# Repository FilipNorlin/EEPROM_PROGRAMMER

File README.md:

# EEPROM_PROGRAMMER

## Diagram

```mermaid
flowchart TD
    BAT(Battery) --> V_REG(Voltage Regulator)
    V_REG --> Protection(Input Protection)
    USB(USB C) --> Protection
    Protection --> MCU{MCU}
    MCU --> LCD(LCD Display)
    MCU --> Input(Input Controls)
    MCU --> SD(SD Card Reader)
    MCU --> Logic(Logic)
    Logic --> LED(Data LEDs)
    Logic --> EEPROM(EEPROM)

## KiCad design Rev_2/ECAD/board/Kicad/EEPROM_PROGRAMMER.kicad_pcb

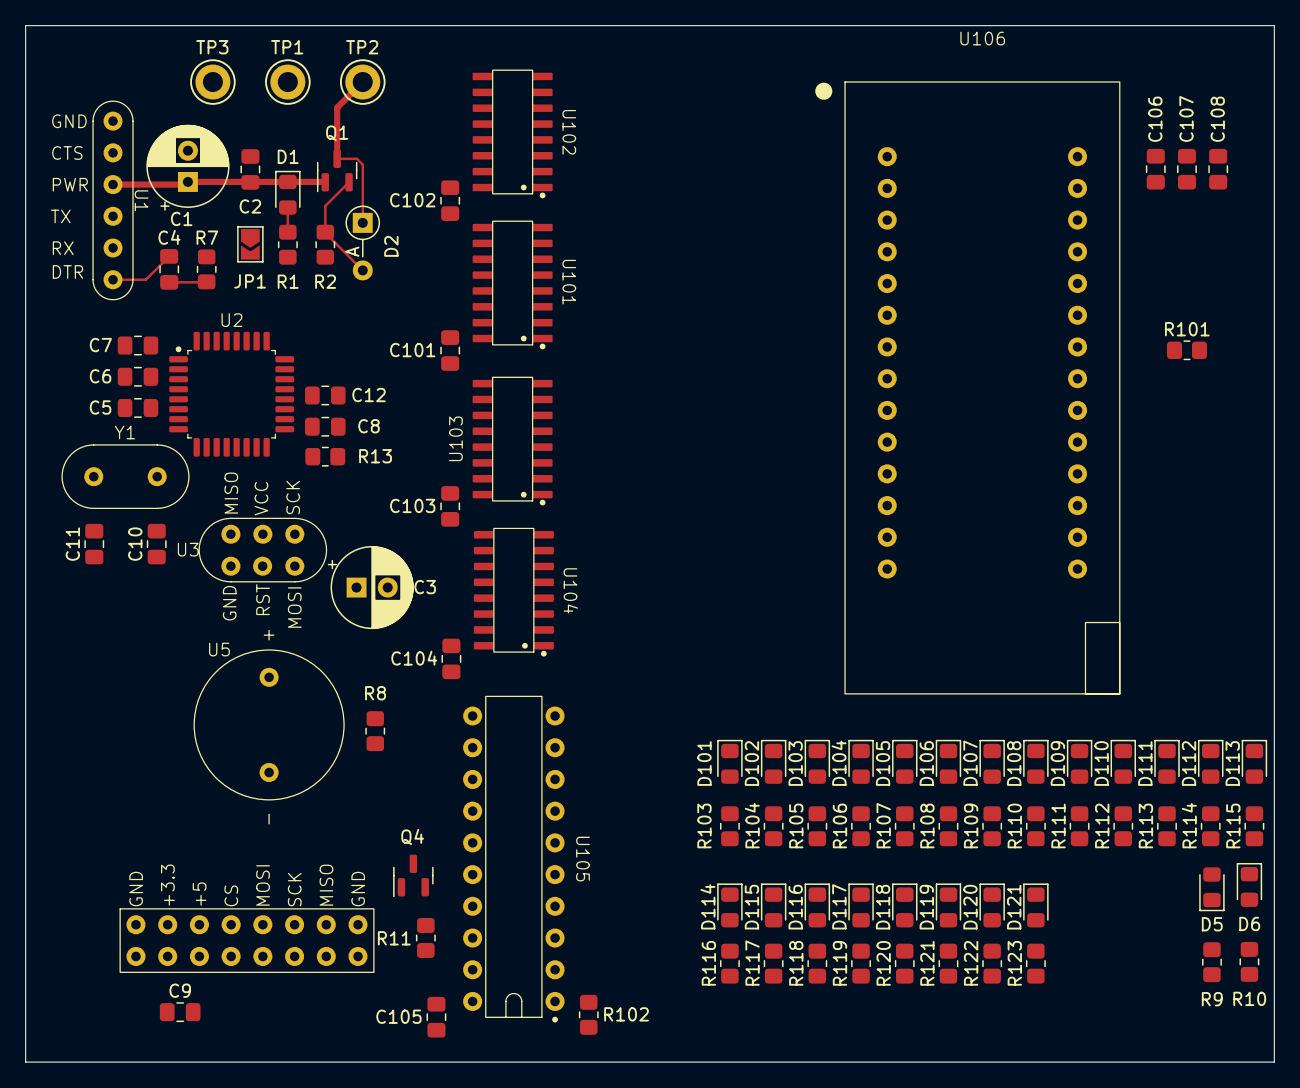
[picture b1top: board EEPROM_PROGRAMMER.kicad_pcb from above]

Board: 4 copper layers, 100.0 x 83.0 mm, 94 parts (0 on the bottom side), 78 nets.

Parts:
C1, C3: 100u; CP_Radial_D6.3mm_P2.50mm
C2, C4, C6, C7, C8, C9, C12, C101, C102, C103, C104, C105, C108: 100n; C_0805_2012Metric_Pad1.18x1.45mm_HandSolder
C5, C106: 4u7; C_0805_2012Metric_Pad1.18x1.45mm_HandSolder
C10, C11: 22p; C_0805_2012Metric_Pad1.18x1.45mm_HandSolder
C107: 1u; C_0805_2012Metric_Pad1.18x1.45mm_HandSolder
D1: RED; LED_0805_2012Metric_Pad1.15x1.40mm_HandSolder
D2: 9V; D_DO-35_SOD27_P3.81mm_Vertical_AnodeUp
D5: READ; LED_0805_2012Metric_Pad1.15x1.40mm_HandSolder
D6: WRITE; LED_0805_2012Metric_Pad1.15x1.40mm_HandSolder
D101, D102, D103, D104, D105, D106, D107, D108, D109, D110, D111, D112, D113: BLUE; LED_0805_2012Metric_Pad1.15x1.40mm_HandSolder
D114, D115, D116, D117, D118, D119, D120, D121: GREEN; LED_0805_2012Metric_Pad1.15x1.40mm_HandSolder
JP1: Jumper; SolderJumper-2_P1.3mm_Open_TrianglePad1.0x1.5mm
Q1: PMOS; SOT-23
Q4: NPN; SOT-23
R1, R2, R9, R10, R103, R104, R105, R106, R107, R108, R109, R110, R111, R112, R113, R114, R115, R116, R117, R118, R119, R120, R121, R122, R123: 4k7; R_0805_2012Metric_Pad1.20x1.40mm_HandSolder
R7, R8, R11, R13, R101, R102: 10k; R_0805_2012Metric_Pad1.20x1.40mm_HandSolder
TP1: PWR; TestPoint_Keystone_5005-5009_Compact
TP2: 5V; TestPoint_Keystone_5005-5009_Compact
TP3: GND; TestPoint_Keystone_5005-5009_Compact
U1: FT232RL
U2: ATMega328P-AU
U3: ICSP
U4: SD_CARD_READER
U5: SUM; Summer
U101, U102, U103, U104: 4076B
U105: 74HC245
U106: AT28C64B-15PU
Y1: 16MHz; Crystal

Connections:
+5V: C5.2, C6.2, C7.2, C8.2, C9.2, C101.1, C102.1, C103.1, C104.1, C105.1, C106.1, C107.1, C108.1, D2.1 (K), JP1.2 (B), Q1.3 (S), R7.1, R13.1, R101.1, TP2.1, U2.4 (VCC), U2.6 (VCC), U2.18 (AVCC), U4.3 (5V), U101.16 (VDD), U102.16 (VDD), U103.16 (VDD), U104.16 (VDD), U105.20 (VCC), U106.28 (VCC)
/D4: U2.2 ((T0)PD4), U106.27 (WE*)
/D5: U2.9 ((T1)PD5), U103.9 (G1), U103.10 (G2), U104.9 (G1), U104.10 (G2)
/D6: U2.10 ((AIN0)D6), U101.9 (G1), U101.10 (G2), U102.9 (G1), U102.10 (G2)
/D7: U2.11 ((AIN1)PD7), U101.7 (CLOCK), U102.7 (CLOCK), U103.7 (CLOCK), U104.7 (CLOCK)
/D8: U2.12 ((ICP)PB0), U101.13 (D2), U103.13 (D2), U105.12 (B6)
/D9: U2.13 ((OC1)PB1), U101.14 (D1), U103.14 (D1), U105.11 (B7)
/D10/SELECT: R11.2, R13.2, U2.14 ((SS)PB2), U4.4 (#CS)
/D11/MOSI: R10.2, U2.15 ((MOSI)PB3), U3.4 (MOSI), U4.5 (MOSI)
/D12/MISO: R9.2, U2.16 ((MISO)PB4), U3.1 (MISO), U4.7 (MISO)
/D13/SCK: R8.2, U2.17 ((SCK)PB5), U3.3 (SCK), U4.6 (SCK)
/D14: U2.23 ((ADC0)PC0), U102.11 (D4), U104.11 (D4), U105.18 (B0)
/D15: U2.24 ((ADC1)PC1), U102.12 (D3), U104.12 (D3), U105.17 (B1)
/D16: U2.25 ((ADC2)PC2), U102.13 (D2), U104.13 (D2), U105.16 (B2)
/D17: U2.26 ((ADC3)PC3), U102.14 (D1), U104.14 (D1), U105.15 (B3)
/D18: U2.27 ((ADC4)PC4), U101.11 (D4), U103.11 (D4), U105.14 (B4)
/D19: U2.28 ((ADC5)PC5), U101.12 (D3), U103.12 (D3), U105.13 (B5)
/DTR: C4.1, U1.6 (DTR)
/EEPROM_LOGIC/A0: R103.1, U101.3 (Q1), U106.10 (A0)
/EEPROM_LOGIC/A1: R104.1, U101.4 (Q2), U106.9 (A1)
/EEPROM_LOGIC/A2: R105.1, U101.5 (Q3), U106.8 (A2)
/EEPROM_LOGIC/A3: R106.1, U101.6 (Q4), U106.7 (A3)
/EEPROM_LOGIC/A4: R107.1, U102.3 (Q1), U106.6 (A4)
/EEPROM_LOGIC/A5: R108.1, U102.4 (Q2), U106.5 (A5)
/EEPROM_LOGIC/A6: R109.1, U102.5 (Q3), U106.4 (A6)
/EEPROM_LOGIC/A7: R110.1, U102.6 (Q4), U106.3 (A7)
/EEPROM_LOGIC/A8: R111.1, U103.3 (Q1), U106.25 (A8)
/EEPROM_LOGIC/A9: R112.1, U103.4 (Q2), U106.24 (A9)
/EEPROM_LOGIC/A10: R113.1, U103.5 (Q3), U106.21 (A10)
/EEPROM_LOGIC/A11: R114.1, U103.6 (Q4), U106.23 (A11)
/EEPROM_LOGIC/A12: R115.1, U104.3 (Q1), U106.2 (A12)
/EEPROM_LOGIC/BUFFER_DIR: R102.2, U104.5 (Q3), U105.1 (DIR)
/EEPROM_LOGIC/BUFFER_OE: U104.6 (Q4), U105.19 (OE)
/EEPROM_LOGIC/EEPROM_OE: R101.2, U104.4 (Q2), U106.22 (OE*)
/EEPROM_LOGIC/I/O0: R116.1, U105.9 (A7), U106.11 (I/O0)
/EEPROM_LOGIC/I/O1: R117.1, U105.8 (A6), U106.12 (I/O1)
/EEPROM_LOGIC/I/O2: R118.1, U105.7 (A5), U106.13 (I/O2)
/EEPROM_LOGIC/I/O3: R119.1, U105.6 (A4), U106.15 (I/O3)
/EEPROM_LOGIC/I/O4: R120.1, U105.5 (A3), U106.16 (I/O4)
/EEPROM_LOGIC/I/O5: R121.1, U105.4 (A2), U106.17 (I/O5)
/EEPROM_LOGIC/I/O6: R122.1, U105.3 (A1), U106.18 (I/O6)
/EEPROM_LOGIC/I/O7: R123.1, U105.2 (A0), U106.19 (I/O7)
/POLARITY_PROTECTION: C1.1, C2.1, C3.1, D1.1 (K), JP1.1 (A), Q1.1 (D), TP1.1, U1.3 (PWR), U3.2 (VCC)
/RESET: C4.2, R7.2, U2.29 (RESET), U3.5 (RST)
/RX-TX: U1.5 (RX), U2.31 ((TXD)PD1)
/SELECT_GND: D5.1 (K), D6.1 (K), Q4.1 (C), U5.2 (-)
/TX-RX: U1.4 (TX), U2.30 ((RXD)PD0)
/VGS: D2.2 (A), Q1.2 (G), R2.1
/XTAL1: C11.2, U2.7 (XTAL1), Y1.1
/XTAL2: C10.2, U2.8 (XTAL2), Y1.2
GND: C1.2, C2.2, C3.2, C5.1, C6.1, C7.1, C8.1, C9.1, C10.1, C11.1, C12.1, C101.2, C102.2, C103.2, C104.2, C105.2, C106.2, C107.2, C108.2, D101.1 (K), D102.1 (K), D103.1 (K), D104.1 (K), D105.1 (K), D106.1 (K), D107.1 (K), D108.1 (K), D109.1 (K), D110.1 (K), D111.1 (K), D112.1 (K), D113.1 (K), D114.1 (K), D115.1 (K), D116.1 (K), D117.1 (K), D118.1 (K), D119.1 (K), D120.1 (K), D121.1 (K), Q4.3 (E), R1.2, R2.2, R102.1, TP3.1, U1.1 (GND), U2.3 (GND), U2.5 (GND), U2.21 (AGND), U3.6 (GND), U4.1 (GND), U101.1 (M), U101.2 (N), U101.8 (VSS), U101.15 (Reset), U102.1 (M), U102.2 (N), U102.8 (VSS), U102.15 (Reset), U103.1 (M), U103.2 (N), U103.8 (VSS), U103.15 (Reset), U104.1 (M), U104.2 (N), U104.8 (VSS), U104.15 (Reset), U105.10 (GND), U106.14 (GND), U106.20 (CE*)
unnamed: D1.2 (A), R1.1
unnamed: D5.2 (A), R9.1
unnamed: D6.2 (A), R10.1
unnamed: D101.2 (A), R103.2
unnamed: D102.2 (A), R104.2
unnamed: D103.2 (A), R105.2
unnamed: D104.2 (A), R106.2
unnamed: D105.2 (A), R107.2
unnamed: D106.2 (A), R108.2
unnamed: D107.2 (A), R109.2
unnamed: D108.2 (A), R110.2
unnamed: D109.2 (A), R111.2
unnamed: D110.2 (A), R112.2
unnamed: D111.2 (A), R113.2
unnamed: D112.2 (A), R114.2
unnamed: D113.2 (A), R115.2
unnamed: D114.2 (A), R116.2
unnamed: D115.2 (A), R117.2
unnamed: D116.2 (A), R118.2
unnamed: D117.2 (A), R119.2
unnamed: D118.2 (A), R120.2
unnamed: D119.2 (A), R121.2
unnamed: D120.2 (A), R122.2
unnamed: D121.2 (A), R123.2
unnamed: Q4.2 (B), R11.1
unnamed: C12.2, U2.20 (AREF)
unnamed: R8.1, U5.1 (+)

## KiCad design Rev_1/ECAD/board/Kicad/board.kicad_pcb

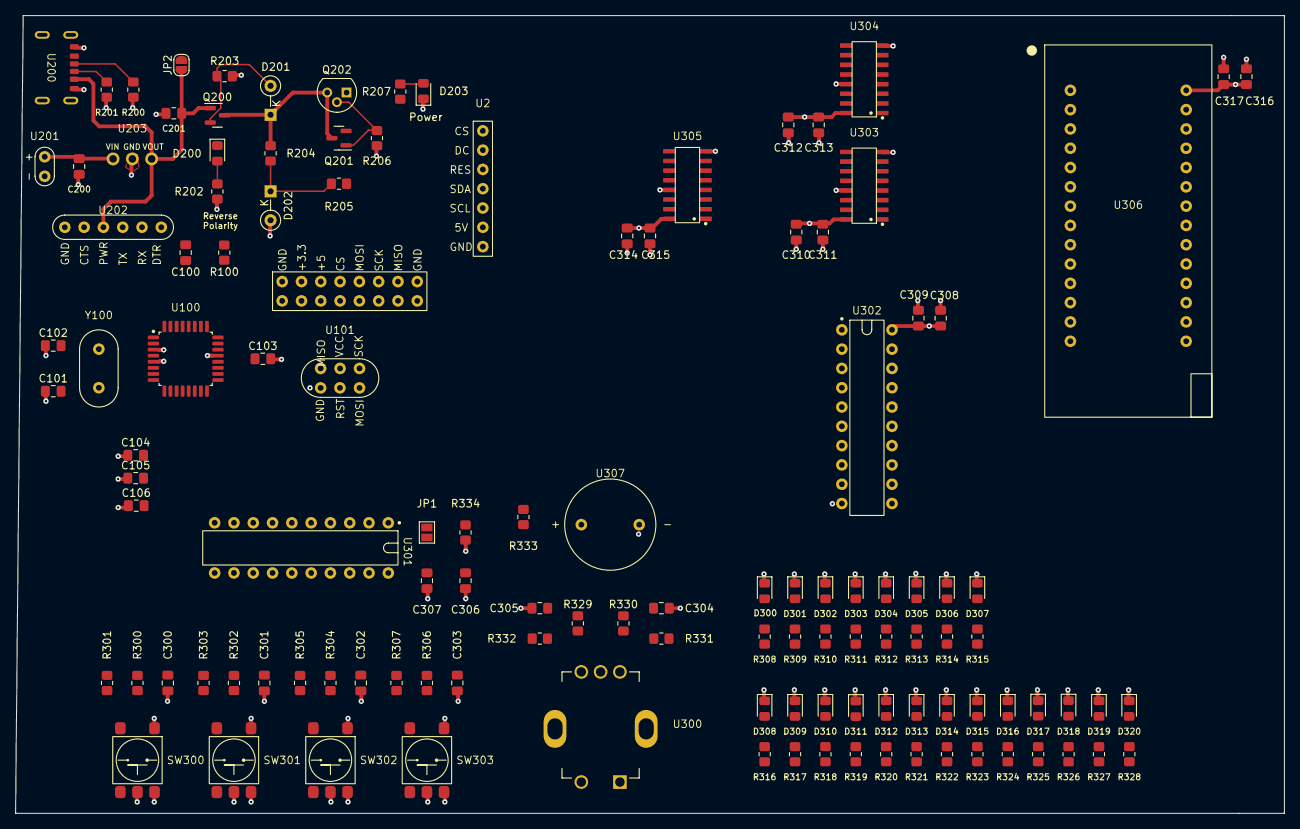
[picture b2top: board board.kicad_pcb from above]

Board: 4 copper layers, 167.0 x 105.0 mm, 122 parts (0 on the bottom side), 101 nets.

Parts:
C100, C103, C201, C304, C305: 100n; C_0805_2012Metric_Pad1.18x1.45mm_HandSolder
C101, C102: 22p; C_0805_2012Metric_Pad1.18x1.45mm_HandSolder
C104, C106, C300, C301, C302, C303, C306, C308, C310, C312, C314, C316: 1u; C_0805_2012Metric_Pad1.18x1.45mm_HandSolder
C105: 4u7; C_0805_2012Metric_Pad1.18x1.45mm_HandSolder
C200: 330n; C_0805_2012Metric_Pad1.18x1.45mm_HandSolder
C307, C309, C311, C313, C315, C317: 10n; C_0805_2012Metric_Pad1.18x1.45mm_HandSolder
D200: RED; LED_0805_2012Metric_Pad1.15x1.40mm_HandSolder
D201: 9V; D_DO-35_SOD27_P3.81mm_Vertical_KathodeUp
D202: 5V6; D_DO-35_SOD27_P3.81mm_Vertical_KathodeUp
D203, D301, D302, D303, D304, D305, D306, D307: GREEN; LED_0805_2012Metric_Pad1.15x1.40mm_HandSolder
D300, D308, D309, D310, D311, D312, D313, D314, D315, D316, D317, D318, D319, D320: BLUE; LED_0805_2012Metric_Pad1.15x1.40mm_HandSolder
JP1: SolderJumper_2_Open; SolderJumper-2_P1.3mm_Open_Pad1.0x1.5mm
JP2: SolderJumper_2_Open; SolderJumper-2_P1.3mm_Open_RoundedPad1.0x1.5mm
Q200: PMOS; SOT-23
Q201: PNP; SOT-23
Q202: PNP; TO-92
R100, R301, R303, R305, R307, R329, R330, R331, R332, R333, R334: 10k; R_0805_2012Metric_Pad1.20x1.40mm_HandSolder
R200, R201, R202, R203, R204, R206, R207, R308, R309, R310, R311, R312, R313, R314, R315, R316, R317, R318, R319, R320, R321, R322, R323, R324, R325, R326, R327, R328: 5k1; R_0805_2012Metric_Pad1.20x1.40mm_HandSolder
R205, R300, R302, R304, R306: 1k; R_0805_2012Metric_Pad1.20x1.40mm_HandSolder
SW300, SW301, SW302, SW303: 6x6; SMD_Button
U1: SD_CARD_READER
U2: LCD OLED; LCD_OLED
U100: ATMega328P-AU
U101: ICSP
U200: USB_C_6PIN
U201: Battery_Connectors
U202: FT232RL
U203: L7805ABV
U300: Rotary_Encoder
U301, U302: 74HC245
U303, U304, U305: 74HC595; 74HC595D
U306: AT28C64B-15PU
U307: Summer
Y100: 16MHZ; Crystal

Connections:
+5V: C104.2, C105.2, C106.2, C306.2, C307.2, C308.2, C309.2, C310.2, C311.2, C312.2, C313.2, C314.2, C315.2, C316.2, C317.2, JP1.2 (B), JP2.2 (B), Q202.1 (C), R100.1, R207.1, R301.1, R303.1, R305.1, R307.1, R331.2, R332.2, U1.3 (5V), U2.2 (5V), U100.4 (VCC), U100.6 (VCC), U100.18 (AVCC), U101.2 (VCC), U300.4 (VCC), U301.20 (VCC), U302.20 (VCC), U303.10 (SRCLR*), U303.16 (VCC), U304.10 (SRCLR*), U304.16 (VCC), U305.10 (SRCLR*), U305.16 (VCC), U306.28 (VCC)
/DC: U2.6 (DC), U100.13 ((OC1)PB1)
/Data Logic/A0: R316.2, U303.1 (QB), U306.10 (A0)
/Data Logic/A1: R317.2, U303.2 (QC), U306.9 (A1)
/Data Logic/A2: R318.2, U303.3 (QD), U306.8 (A2)
/Data Logic/A3: R319.2, U303.4 (QE), U306.7 (A3)
/Data Logic/A4: R320.2, U303.5 (QF), U306.6 (A4)
/Data Logic/A5: R321.2, U303.6 (QG), U306.5 (A5)
/Data Logic/A6: R322.2, U303.7 (QH), U306.4 (A6)
/Data Logic/A7: R323.2, U304.1 (QB), U306.3 (A7)
/Data Logic/A8: R324.2, U304.2 (QC), U306.25 (A8)
/Data Logic/A9: R325.2, U304.3 (QD), U306.24 (A9)
/Data Logic/A10: R326.2, U304.4 (QE), U306.21 (A10)
/Data Logic/A11: R327.2, U304.5 (QF), U306.23 (A11)
/Data Logic/A12: R328.2, U304.6 (QG), U306.2 (A12)
/Data Logic/BUTTON_1: C300.2, R300.2, R301.2, U301.13 (B5)
/Data Logic/BUTTON_2: C301.2, R302.2, R303.2, U301.14 (B4)
/Data Logic/BUTTON_3: C302.2, R304.2, R305.2, U301.15 (B3)
/Data Logic/BUTTON_4: C303.2, R306.2, R307.2, U301.16 (B2)
/Data Logic/D0: R308.2, U302.18 (B0), U306.11 (I/O0)
/Data Logic/D1: R309.2, U302.17 (B1), U306.12 (I/O1)
/Data Logic/D2: R310.2, U302.16 (B2), U306.13 (I/O2)
/Data Logic/D3: R311.2, U302.15 (B3), U306.15 (I/O3)
/Data Logic/D4: R312.2, U302.14 (B4), U306.16 (I/O4)
/Data Logic/D5: R313.2, U302.13 (B5), U306.17 (I/O5)
/Data Logic/D6: R314.2, U302.12 (B6), U306.18 (I/O6)
/Data Logic/D7: R315.2, U302.11 (B7), U306.19 (I/O7)
/Data Logic/DATA_BUFFER_DIR: U302.1 (DIR), U305.4 (QE)
/Data Logic/DATA_BUFFER_OE: U302.19 (OE), U305.5 (QF)
/Data Logic/EEPROM_OE*: U305.3 (QD), U306.22 (OE*)
/Data Logic/INPUT_BUFFER_OE: U301.19 (OE), U305.2 (QC)
/Data Logic/ROT_A: R330.1, R331.1, U300.2 (A)
/Data Logic/ROT_A_INPT: C304.2, R330.2, U301.17 (B1)
/Data Logic/ROT_B: R329.1, R332.1, U300.3 (B)
/Data Logic/ROT_B_INPT: C305.2, R329.2, U301.18 (B0)
/Data Logic/SER_CASCADE_1: U303.9 (QH'), U304.14 (SER)
/Data Logic/SER_CASCADE_2: U304.9 (QH'), U305.14 (SER)
/Data Logic/Summer: R333.2, U307.1 (+)
/Data Logic/Summer_CL: R333.1, U305.1 (QB)
/EEPROM_WE*: U100.28 ((ADC5)PC5), U306.27 (WE*)
/I/O0: U100.25 ((ADC2)PC2), U301.2 (A0), U302.2 (A0)
/I/O1: U100.26 ((ADC3)PC3), U301.3 (A1), U302.3 (A1)
/I/O2: U100.32 ((INT0)PD2), U301.4 (A2), U302.4 (A2)
/I/O3: U100.1 ((INT1)PD3), U301.5 (A3), U302.5 (A3)
/I/O4: U100.2 ((T0)PD4), U301.6 (A4), U302.6 (A4)
/I/O5: U100.9 ((T1)PD5), U301.7 (A5), U302.7 (A5)
/I/O6: U100.10 ((AIN0)D6), U301.8 (A6), U302.8 (A6)
/I/O7: U100.11 ((AIN1)PD7), U301.9 (A7), U302.9 (A7)
/MCU/AREF: C103.1, U100.20 (AREF)
/MCU/DTR: C100.1, U202.6 (DTR)
/MCU/RESET: C100.2, R100.2, U100.29 (RESET), U101.5 (RST)
/MCU/RX/TX: U100.31 ((TXD)PD1), U202.5 (RX)
/MCU/TX/RX: U100.30 ((RXD)PD0), U202.4 (TX)
/MCU/XTAL1: C102.2, U100.7 (XTAL1), Y100.1
/MCU/XTAL2: C101.2, U100.8 (XTAL2), Y100.2
/MISO/SDA: U1.7 (MISO), U2.4 (SDA), U100.16 ((MISO)PB4), U101.1 (MISO)
/MOSI/RES: U1.5 (MOSI), U2.5 (RES), U100.15 ((MOSI)PB3), U101.4 (MOSI)
/OLED_CS: U2.7 (CS), U100.12 ((ICP)PB0)
/SCK/SCL: U1.6 (SCK), U2.3 (SCL), U100.17 ((SCK)PB5), U101.3 (SCK)
/SD_CS: U1.4 (CS), U100.14 ((SS)PB2)
/SHIFT_RCLK: U100.27 ((ADC4)PC4), U303.12 (RCLK), U304.12 (RCLK), U305.12 (RCLK)
/SHIFT_SER: U100.24 ((ADC1)PC1), U303.14 (SER)
/SHIFT_SRCLK: U100.23 ((ADC0)PC0), U303.11 (SRCLK), U304.11 (SRCLK), U305.11 (SRCLK)
/Voltage Input/5V_REGULATED: C201.2, D200.1 (K), JP2.1 (A), Q200.1 (D), U200.2 (VBUS), U200.5 (VBUS), U202.3 (PWR), U203.3 (VOUT)
/Voltage Input/BATTERY_INPUT: C200.2, U201.1 (+), U203.1 (VIN)
/Voltage Input/POLARITY_PROTECTED: D201.1 (K), Q200.3 (S), Q201.3 (E), Q202.3 (E), R204.1
/Voltage Input/USB_CC1: R200.1, U200.3 (CC1)
/Voltage Input/USB_CC2: R201.1, U200.4 (CC2)
/Voltage Input/VGS: D201.2 (A), Q200.2 (G), R203.1
GND: C101.1, C102.1, C103.2, C104.1, C105.1, C106.1, C200.1, C201.1, C300.1, C301.1, C302.1, C303.1, C304.1, C305.1, C306.1, C307.1, C308.1, C309.1, C310.1, C311.1, C312.1, C313.1, C314.1, C315.1, C316.1, C317.1, D202.2 (A), D203.1 (K), D300.1 (K), D301.1 (K), D302.1 (K), D303.1 (K), D304.1 (K), D305.1 (K), D306.1 (K), D307.1 (K), D308.1 (K), D309.1 (K), D310.1 (K), D311.1 (K), D312.1 (K), D313.1 (K), D314.1 (K), D315.1 (K), D316.1 (K), D317.1 (K), D318.1 (K), D319.1 (K), D320.1 (K), R200.2, R201.2, R202.2, R203.2, R206.2, R334.2, SW300.1, SW300.3 (GND), SW301.1, SW301.3 (GND), SW302.1, SW302.3 (GND), SW303.1, SW303.3 (GND), U1.1 (GND), U2.1 (GND), U100.3 (GND), U100.5 (GND), U100.21 (AGND), U101.6 (GND), U200.1 (GND), U200.6 (GND), U201.2 (-), U202.1 (GND), U203.2 (GND), U300.1 (GND), U301.10 (GND), U301.11 (B7), U301.12 (B6), U302.10 (GND), U303.8 (GND), U303.13 (OE*), U304.8 (GND), U304.13 (OE*), U305.8 (GND), U305.13 (OE*), U306.14 (GND), U306.20 (CE*), U307.2 (-)
unnamed: D200.2 (A), R202.1
unnamed: D202.1 (K), R204.2, R205.1
unnamed: D203.2 (A), R207.2
unnamed: D300.2 (A), R308.1
unnamed: D301.2 (A), R309.1
unnamed: D302.2 (A), R310.1
unnamed: D303.2 (A), R311.1
unnamed: D304.2 (A), R312.1
unnamed: D305.2 (A), R313.1
unnamed: D306.2 (A), R314.1
unnamed: D307.2 (A), R315.1
unnamed: D308.2 (A), R316.1
unnamed: D309.2 (A), R317.1
unnamed: D310.2 (A), R318.1
unnamed: D311.2 (A), R319.1
unnamed: D312.2 (A), R320.1
unnamed: D313.2 (A), R321.1
unnamed: D314.2 (A), R322.1
unnamed: D315.2 (A), R323.1
unnamed: D316.2 (A), R324.1
unnamed: D317.2 (A), R325.1
unnamed: D318.2 (A), R326.1
unnamed: D319.2 (A), R327.1
unnamed: D320.2 (A), R328.1
unnamed: JP1.1 (A), R334.1, U301.1 (DIR)
unnamed: Q201.2 (B), R205.2
unnamed: Q201.1 (C), Q202.2 (B), R206.1
unnamed: R300.1, SW300.2
unnamed: R302.1, SW301.2
unnamed: R304.1, SW302.2
unnamed: R306.1, SW303.2

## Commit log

2024-05-30 Migrate to Mac
2024-06-08 Added atemga328P-AU symbol
2024-06-09 test
2024-06-09 Removed git_info.py
2024-06-09 Auto commit by interactive_git.py
2024-06-09 Remove files specified in .gitignore
2024-06-09 Updated Aatmega 328p symbol and added FT232 symbol
2024-06-09 Added MCU sketch
2024-06-09 Added ICSP symbol
2024-06-09 Added USB_C 6PIN symbol
2024-06-09 Added USB Power circiut
2024-06-18 Added SD CARD READER symbol
2024-06-22 Added power unit, and started on the logic block
2024-06-29 Added AT28C64B-15PU
2024-06-29 Updated net-name on Data Logic sheet
2024-06-29 Added Bus aswell as data logic for the eeprom
2024-06-30 LICENSE
2024-06-30 Updating .gitignore
2024-06-30 Added Rotary encoder and buttons to the Input Buffer
2024-06-30 Added 74HC595 symbol
2024-06-30 Added Rotary encoder Symbol
2024-07-25 Updated gitignore
2024-09-18 Updating Bus wiring
2024-09-25 Updated Symbol library´and added SD Card Reader to schematic
2024-09-25 Added 74HC595 footprint
2024-09-26 Added footprint 74HC245 and 4076B
2024-09-26 Removed unwanted footprint
2024-09-27 Added marker for pin 1 on 74HC245
2024-09-27 Linked some of the symbols to its footprint
2024-09-27 Added 3d models to footprint
2024-09-27 Added Zif socket
2024-09-27 Added Atmega328P-AU Footprint and 3d model
2024-09-27 Added Connectors
2024-10-16 Removed I2C Display and added an SPI Display instead
2024-10-16 Add fp-lib-table to track
2024-10-18 Changes current limiting resistors for LEDS to 5k1 ohms
2024-10-19 Added Usb-C Footprint
2024-10-19 Added 7805ABV and SD_CARD_READER
2024-10-19 Updated Data Logic sheet
2024-10-19 Added Rotary Encoder
2024-10-20 Changed from 4-bit registers to shift registers
2024-10-21 Created a pcb file and added labels to footprints
2024-10-21 Resolved changes
2024-10-21 Added Bypass Capacitors
2024-10-21 Updated Bypass Capacitors Label
2024-10-21 Set up PCB configurations
2024-10-21 Made a ruf idea of the input protection on the pcb
2024-11-16 Sorted most of the individual circuitri, time to start putting it all togheter
2024-11-16 Layed out the input power circuit
2024-11-16 Made changes to the wiring in the shcematic to make it easier to route on the pcb, U305
2024-11-16 Made some progress on the pcb
2024-11-16 Most of the things are put to its place, LED indicators still needs some configuration, and som testpoints should be added!
2024-11-27 Changed the footprint on D201 and D202 to DO-35_SOD27
2024-12-07 Updated Zif socket to right dimensions
2024-12-07 Everything finished, can start routing
2024-12-07 Added cutout to the pcb
2024-12-07 Most of the GND vias are in place and the power section is mostly done
2025-03-12 Copied libraries from Rev1 to Rev2
2025-03-12 Added data and voltage input with FTDI
2025-03-12 Added Reverse Polarity Protection and Overvoltage Portection
2025-03-13 Added Atmega328 to the schematic
2025-03-13 Added SD-Card Reader to schematic
2025-03-13 Change SD-Card Reader Chip select to active low
2025-03-13 Change Summer symbol color to yellow
2025-03-13 Adde Summer, Read-LED, Write-LED
2025-03-19 Added registers for the EEPROM
2025-03-20 Added a sheet page for EEPROM_LOGIC
2025-03-20 Finished most of EEPROM LOGIC
2025-03-20 Atmega to logic wiring completed
2025-03-21 Added Bypass capacitors aswell as pullup resistors
2025-04-22 Removed overvoltage protection for now
2025-04-22 Ready for PCB-Design
2025-04-22 Set up bases of board configurations
2025-04-22 Added missing 3D-models aswell as fixed wrong footprints
2025-04-23 Done with inital layout
